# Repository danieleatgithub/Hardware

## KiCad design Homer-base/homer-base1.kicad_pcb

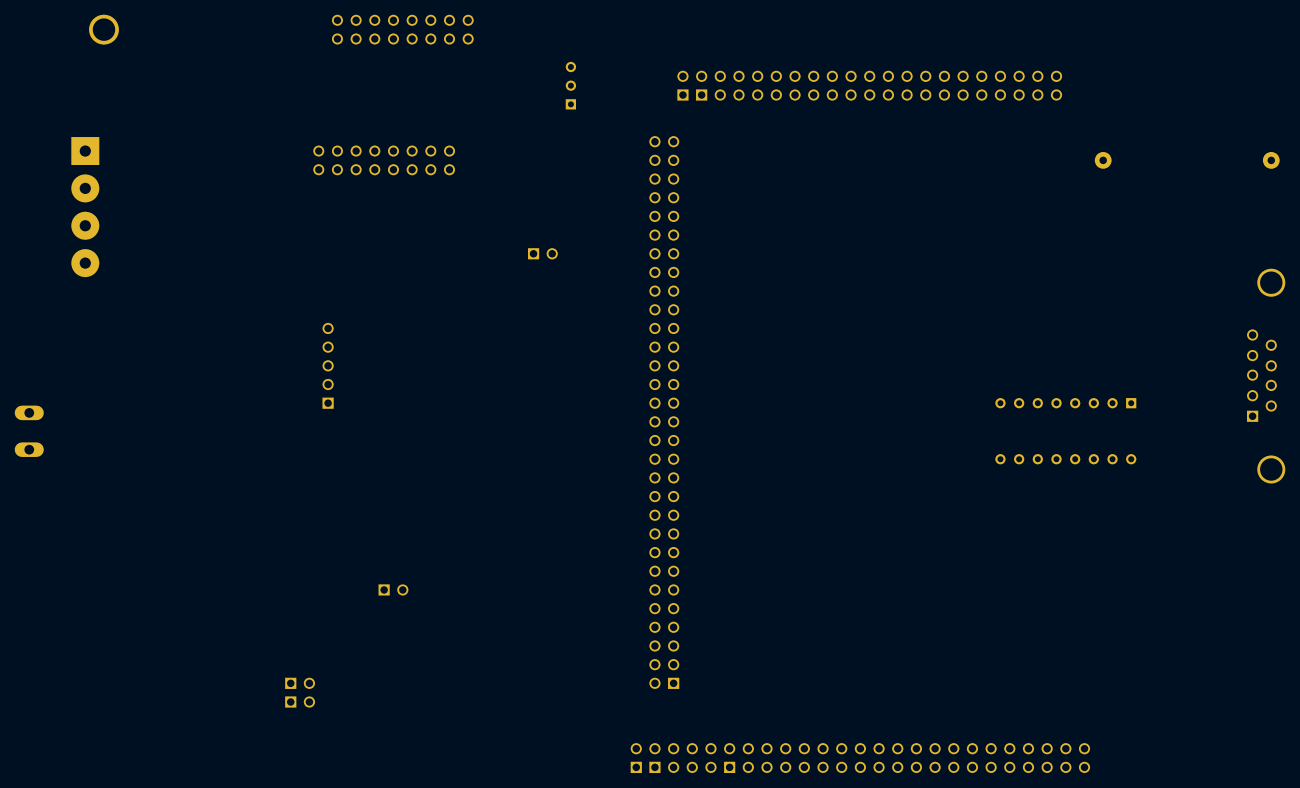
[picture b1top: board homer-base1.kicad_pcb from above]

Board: 2 copper layers, 11 parts (0 on the bottom side), 3 nets, no tracks yet.

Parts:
1PIN: P***; 1pin
CR2032H: VAL**; CR2032H
DB9MC: VAL**; DB9MC
I2C TP: Val**; PIN_ARRAY_2X1
J2: PIN_ARRAY_30X2
P: 5V OUT; AK300-2
P***: BORN4; bornier4
PIN_ARRAY_2: Val**; PIN_ARRAY_2X1
POWER TPs: Val**; PIN_ARRAY_5x1
RS232: Val**; PIN_ARRAY_2X1
U***: MAX232; DIP-16__300

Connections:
GND: J2.2, J2.30, J2.32
PA15_1: J2.18, J2.28
VCC: J2.29, J2.31

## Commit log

2015-11-15 First ccommit
2015-11-15 add readme
2015-12-02 first release
2015-12-02 Homer-base
2015-12-02 front-panel
2015-12-02 humidity
2015-12-03 Kicad
2015-12-03 fix my custom library
2016-01-02 Add level converter and other fix
2016-01-02 Add level converter
2016-01-02 Fix connector and power labels
2016-01-02 Add output to git
2016-01-02 add gtignore
2017-02-11 Add varistor and AC/DC
2017-02-11 add varistor and AC/DC converter
2017-02-12 New power supply subsystem
2017-04-18 Add current sensor, RTC battery, Power protection
2017-06-10 Power revision and add ina219 sensor
2017-06-11 Fix Power schematics
2017-06-18 fix adc vref
2017-07-30 level shifter revision and frequency calibration
2017-07-30 ignore files
2017-08-22 Add Margie testboard layout
2017-08-26 Add humidity sensors
